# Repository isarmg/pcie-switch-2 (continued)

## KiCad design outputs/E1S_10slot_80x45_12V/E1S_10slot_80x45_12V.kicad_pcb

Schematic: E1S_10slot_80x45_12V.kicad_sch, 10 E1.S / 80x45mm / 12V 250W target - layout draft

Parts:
C1, C2: 10uF 25V X7R; C_1210_3225Metric
C101, C104, C107, C110, C113, C116, C119, C122, C125, C128, C301: 10nF 25V; C_0402_1005Metric
C102, C105, C108, C111, C114, C117, C120, C123, C126, C129: 100nF 50V; C_0603_1608Metric
C103, C106, C109, C112, C115, C118, C121, C124, C127, C130: 1uF 25V; C_0603_1608Metric
C311: 10uF 25V; C_0805_2012Metric
C312: 100nF 50V; C_0402_1005Metric
C313: 3.3nF 25V; C_0402_1005Metric
C314, C315: 47uF 16V; C_1210_3225Metric
D1, D2: SMBJ13CA; D_SMB
F1, F2: 20A 125V; Littelfuse_456_20A
J1, J2, J3, J4, J5, J6, J7, J8, J9, J10: HSEC6-028-01-S-DV-WT-TR; Samtec_HSEC6-028-01-S-DV-WT
J11: 12V 15A FEED A; WireSolder_2x_8x5_P12
J12: 12V 15A FEED B; WireSolder_2x_8x5_P12
L31: 2.2uH; L_Coilcraft_XAL4020-XXX
R101, R106, R111, R116, R121, R126, R131, R136, R141, R146, R301: 76.1k; R_0402_1005Metric
R102, R104, R107, R109, R112, R114, R117, R119, R122, R124, R127, R129, R132, R134, R137, R139, R142, R144, R147, R149, R302, R304: 10k; R_0402_1005Metric
R103, R108, R113, R118, R123, R128, R133, R138, R143, R148, R303: 102k; R_0402_1005Metric
R105, R110, R115, R120, R125, R130, R135, R140, R145, R150: 1.10k; R_0402_1005Metric
R305: 3.32k; R_0402_1005Metric
R311: 100k; R_0402_1005Metric
U1: FICTITIOUS_BGA256_RANDOM_PINOUT; FICTITIOUS_BGA256_37p5_P1_Sparse32_RANDOM
U11, U12, U13, U14, U15, U16, U17, U18, U19, U20, U30: TPS259470ARPWR; TI_RPW0010A_TPS25947
U31: TPS62132RGTR; VQFN-16-1EP_3x3mm_P0.5mm_EP1.68x1.68mm

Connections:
/AUX_12V_PROTECTED: C311.1, C312.1, U30.6 (OUT), U31.10, U31.11, U31.12, U31.13
/AUX_DVDT: C301.1, U30.7 (DVDT)
/AUX_ILM: R305.1, U30.9 (ILM)
/AUX_OV: R303.2, R304.1, U30.2 (OVLO)
/AUX_PG: R311.2, U31.4
/AUX_UV: R301.2, R302.1, U30.1 (EN_UVLO)
/BUCK_SS: C313.1, U31.9
/BUCK_SW: L31.1, U31.1, U31.2, U31.3
/GND: C1.2, C2.2, C101.2, C102.2, C103.2, C104.2, C105.2, C106.2, C107.2, C108.2, C109.2, C110.2, C111.2, C112.2, C113.2, C114.2, C115.2, C116.2, C117.2, C118.2, C119.2, C120.2, C121.2, C122.2, C123.2, C124.2, C125.2, C126.2, C127.2, C128.2, C129.2, C130.2, C301.2, C311.2, C312.2, C313.2, C314.2, C315.2, D1.2, D2.2, J1.A1, J1.A2, J1.A3, J1.A4, J1.A5, J1.A6, J1.A13, J1.A16, J1.A19, J1.A22, J1.A25, J1.A28, J1.B13, J1.B16, J1.B19, J1.B22, J1.B25, J1.B28, J2.A1, J2.A2, J2.A3, J2.A4, J2.A5, J2.A6, J2.A13, J2.A16, J2.A19, J2.A22, J2.A25, J2.A28, J2.B13, J2.B16, J2.B19, J2.B22, J2.B25, J2.B28, J3.A1, J3.A2, J3.A3, J3.A4, J3.A5, J3.A6, J3.A13, J3.A16, J3.A19, J3.A22, J3.A25, J3.A28, J3.B13, J3.B16, J3.B19, J3.B22, J3.B25, J3.B28, J4.A1, J4.A2, J4.A3, J4.A4, J4.A5, J4.A6, J4.A13, J4.A16, J4.A19, J4.A22, J4.A25, J4.A28, J4.B13, J4.B16, J4.B19, J4.B22, J4.B25, J4.B28, J5.A1, J5.A2, J5.A3, J5.A4, J5.A5, J5.A6, J5.A13, J5.A16, J5.A19, J5.A22, J5.A25, J5.A28, J5.B13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
/P3V3_AUX: C314.1, C315.1, J1.B11, J2.B11, J3.B11, J4.B11, J5.B11, J6.B11, J7.B11, J8.B11, J9.B11, J10.B11, L31.2, R311.1, U31.14
/P12_SLOT01: C103.1, J1.B1, J1.B2, J1.B3, J1.B4, J1.B5, J1.B6, U11.6 (OUT)
/P12_SLOT02: C106.1, J2.B1, J2.B2, J2.B3, J2.B4, J2.B5, J2.B6, U12.6 (OUT)
/P12_SLOT03: C109.1, J3.B1, J3.B2, J3.B3, J3.B4, J3.B5, J3.B6, U13.6 (OUT)
/P12_SLOT04: C112.1, J4.B1, J4.B2, J4.B3, J4.B4, J4.B5, J4.B6, U14.6 (OUT)
/P12_SLOT05: C115.1, J5.B1, J5.B2, J5.B3, J5.B4, J5.B5, J5.B6, U15.6 (OUT)
/P12_SLOT06: C118.1, J6.B1, J6.B2, J6.B3, J6.B4, J6.B5, J6.B6, U16.6 (OUT)
/P12_SLOT07: C121.1, J7.B1, J7.B2, J7.B3, J7.B4, J7.B5, J7.B6, U17.6 (OUT)
/P12_SLOT08: C124.1, J8.B1, J8.B2, J8.B3, J8.B4, J8.B5, J8.B6, U18.6 (OUT)
/P12_SLOT09: C127.1, J9.B1, J9.B2, J9.B3, J9.B4, J9.B5, J9.B6, U19.6 (OUT)
/P12_SLOT10: C130.1, J10.B1, J10.B2, J10.B3, J10.B4, J10.B5, J10.B6, U20.6 (OUT)
/S01_DUALPORTEN_N: J1.B9
/S01_LED: J1.A10
/S01_PERST0_N: J1.B10, U1.F23
/S01_PERST1_CLKREQ_N: J1.A11
/S01_PRSNT0_N: J1.A12
/S01_PWRDIS: J1.B12
/S01_PWR_DVDT: C101.1, U11.7 (DVDT)
/S01_PWR_ILM: R105.1, U11.9 (ILM)
/S01_PWR_OV: R103.2, R104.1, U11.2 (OVLO)
/S01_PWR_UV: R101.2, R102.1, U11.1 (EN_UVLO)
/S01_REFCLK0_N: J1.B14, U1.C19
/S01_REFCLK0_P: J1.B15, U1.C20
/S01_REFCLK1_N: J1.A14, U1.AF13
/S01_REFCLK1_P: J1.A15, U1.AF14
/S01_SMBCLK_I3CCLK: J1.A7
/S01_SMBDATA_I3CDATA: J1.A8
/S01_SMRST_N: J1.A9
/S01_SW_RX0_N: J1.A17, U1.C7
/S01_SW_RX0_P: J1.A18, U1.C8
/S01_SW_RX1_N: J1.A20, U1.AK1
/S01_SW_RX1_P: J1.A21, U1.AK2
/S01_SW_RX2_N: J1.A23, U1.AJ31
/S01_SW_RX2_P: J1.A24, U1.AJ32
/S01_SW_RX3_N: J1.A26, U1.B5
/S01_SW_RX3_P: J1.A27, U1.B6
/S01_SW_TX0_N: J1.B17, U1.AF5
/S01_SW_TX0_P: J1.B18, U1.AF6
/S01_SW_TX1_N: J1.B20, U1.B1
/S01_SW_TX1_P: J1.B21, U1.B2
/S01_SW_TX2_N: J1.B23, U1.AL23
/S01_SW_TX2_P: J1.B24, U1.AL24
/S01_SW_TX3_N: J1.B26, U1.AH9
/S01_SW_TX3_P: J1.B27, U1.AH10
/S02_DUALPORTEN_N: J2.B9
/S02_LED: J2.A10
/S02_PERST0_N: J2.B10, U1.F24
/S02_PERST1_CLKREQ_N: J2.A11
/S02_PRSNT0_N: J2.A12
/S02_PWRDIS: J2.B12
/S02_PWR_DVDT: C104.1, U12.7 (DVDT)
/S02_PWR_ILM: R110.1, U12.9 (ILM)
/S02_PWR_OV: R108.2, R109.1, U12.2 (OVLO)
/S02_PWR_UV: R106.2, R107.1, U12.1 (EN_UVLO)
/S02_REFCLK0_N: J2.B14, U1.AL13
/S02_REFCLK0_P: J2.B15, U1.AL14
/S02_REFCLK1_N: J2.A14, U1.AM21
/S02_REFCLK1_P: J2.A15, U1.AM22
/S02_SMBCLK_I3CCLK: J2.A7
/S02_SMBDATA_I3CDATA: J2.A8
/S02_SMRST_N: J2.A9
/S02_SW_RX0_N: J2.A17, U1.AM25
/S02_SW_RX0_P: J2.A18, U1.AM26
/S02_SW_RX1_N: J2.A20, U1.AL17
/S02_SW_RX1_P: J2.A21, U1.AL18
/S02_SW_RX2_N: J2.A23, U1.C5
/S02_SW_RX2_P: J2.A24, U1.C6
/S02_SW_RX3_N: J2.A26, U1.AK23
/S02_SW_RX3_P: J2.A27, U1.AK24
/S02_SW_TX0_N: J2.B17, U1.AL25
/S02_SW_TX0_P: J2.B18, U1.AL26
/S02_SW_TX1_N: J2.B20, U1.B31
/S02_SW_TX1_P: J2.B21, U1.B32
/S02_SW_TX2_N: J2.B23, U1.AM7
/S02_SW_TX2_P: J2.B24, U1.AM8
/S02_SW_TX3_N: J2.B26, U1.AH23
/S02_SW_TX3_P: J2.B27, U1.AH24
/S03_DUALPORTEN_N: J3.B9
/S03_LED: J3.A10
/S03_PERST0_N: J3.B10, U1.F17
/S03_PERST1_CLKREQ_N: J3.A11
/S03_PRSNT0_N: J3.A12
/S03_PWRDIS: J3.B12
/S03_PWR_DVDT: C107.1, U13.7 (DVDT)
/S03_PWR_ILM: R115.1, U13.9 (ILM)
/S03_PWR_OV: R113.2, R114.1, U13.2 (OVLO)
/S03_PWR_UV: R111.2, R112.1, U13.1 (EN_UVLO)
/S03_REFCLK0_N: J3.B14, U1.D23
/S03_REFCLK0_P: J3.B15, U1.D24
/S03_REFCLK1_N: J3.A14, U1.B9
/S03_REFCLK1_P: J3.A15, U1.B10
/S03_SMBCLK_I3CCLK: J3.A7
/S03_SMBDATA_I3CDATA: J3.A8
/S03_SMRST_N: J3.A9
/S03_SW_RX0_N: J3.A17, U1.AG15
/S03_SW_RX0_P: J3.A18, U1.AG16
/S03_SW_RX1_N: J3.A20, U1.C13
/S03_SW_RX1_P: J3.A21, U1.C14
/S03_SW_RX2_N: J3.A23, U1.C21
/S03_SW_RX2_P: J3.A24, U1.C22
/S03_SW_RX3_N: J3.A26, U1.A1
/S03_SW_RX3_P: J3.A27, U1.A2
/S03_SW_TX0_N: J3.B17, U1.AL11
/S03_SW_TX0_P: J3.B18, U1.AL12
/S03_SW_TX1_N: J3.B20, U1.D9
/S03_SW_TX1_P: J3.B21, U1.D10
/S03_SW_TX2_N: J3.B23, U1.AH1
/S03_SW_TX2_P: J3.B24, U1.AH2
/S03_SW_TX3_N: J3.B26, U1.D17
/S03_SW_TX3_P: J3.B27, U1.D18
/S04_DUALPORTEN_N: J4.B9
/S04_LED: J4.A10
/S04_PERST0_N: J4.B10, U1.F18
/S04_PERST1_CLKREQ_N: J4.A11
/S04_PRSNT0_N: J4.A12
/S04_PWRDIS: J4.B12
/S04_PWR_DVDT: C110.1, U14.7 (DVDT)
/S04_PWR_ILM: R120.1, U14.9 (ILM)
/S04_PWR_OV: R118.2, R119.1, U14.2 (OVLO)
/S04_PWR_UV: R116.2, R117.1, U14.1 (EN_UVLO)
/S04_REFCLK0_N: J4.B14, U1.AL3
/S04_REFCLK0_P: J4.B15, U1.AL4
/S04_REFCLK1_N: J4.A14, U1.AG17
/S04_REFCLK1_P: J4.A15, U1.AG18
/S04_SMBCLK_I3CCLK: J4.A7
/S04_SMBDATA_I3CDATA: J4.A8
/S04_SMRST_N: J4.A9
/S04_SW_RX0_N: J4.A17, U1.AH7
/S04_SW_RX0_P: J4.A18, U1.AH8
/S04_SW_RX1_N: J4.A20, U1.AF21
/S04_SW_RX1_P: J4.A21, U1.AF22
/S04_SW_RX2_N: J4.A23, U1.AM31
/S04_SW_RX2_P: J4.A24, U1.AM32
/S04_SW_RX3_N: J4.A26, U1.E31
/S04_SW_RX3_P: J4.A27, U1.E32
/S04_SW_TX0_N: J4.B17, U1.AF17
/S04_SW_TX0_P: J4.B18, U1.AF18
/S04_SW_TX1_N: J4.B20, U1.AM27
/S04_SW_TX1_P: J4.B21, U1.AM28
/S04_SW_TX2_N: J4.B23, U1.AF3
/S04_SW_TX2_P: J4.B24, U1.AF4
/S04_SW_TX3_N: J4.B26, U1.AK7
/S04_SW_TX3_P: J4.B27, U1.AK8
/S05_DUALPORTEN_N: J5.B9
/S05_LED: J5.A10
/S05_PERST0_N: J5.B10, U1.AH15
/S05_PERST1_CLKREQ_N: J5.A11
/S05_PRSNT0_N: J5.A12
/S05_PWRDIS: J5.B12
/S05_PWR_DVDT: C113.1, U15.7 (DVDT)
/S05_PWR_ILM: R125.1, U15.9 (ILM)
/S05_PWR_OV: R123.2, R124.1, U15.2 (OVLO)
/S05_PWR_UV: R121.2, R122.1, U15.1 (EN_UVLO)
/S05_REFCLK0_N: J5.B14, U1.A17
/S05_REFCLK0_P: J5.B15, U1.A18
/S05_REFCLK1_N: J5.A14, U1.AM29
/S05_REFCLK1_P: J5.A15, U1.AM30
/S05_SMBCLK_I3CCLK: J5.A7
/S05_SMBDATA_I3CDATA: J5.A8
/S05_SMRST_N: J5.A9
/S05_SW_RX0_N: J5.A17, U1.C23
/S05_SW_RX0_P: J5.A18, U1.C24
/S05_SW_RX1_N: J5.A20, U1.A25
/S05_SW_RX1_P: J5.A21, U1.A26
/S05_SW_RX2_N: J5.A23, U1.AL27
/S05_SW_RX2_P: J5.A24, U1.AL28
/S05_SW_RX3_N: J5.A26, U1.AJ15
/S05_SW_RX3_P: J5.A27, U1.AJ16
/S05_SW_TX0_N: J5.B17, U1.D7
/S05_SW_TX0_P: J5.B18, U1.D8
/S05_SW_TX1_N: J5.B20, U1.C1
/S05_SW_TX1_P: J5.B21, U1.C2
/S05_SW_TX2_N: J5.B23, U1.AM17
/S05_SW_TX2_P: J5.B24, U1.AM18
/S05_SW_TX3_N: J5.B26, U1.B21
/S05_SW_TX3_P: J5.B27, U1.B22
/S06_DUALPORTEN_N: J6.B9
/S06_LED: J6.A10
/S06_PERST0_N: J6.B10, U1.AH16
/S06_PERST1_CLKREQ_N: J6.A11
/S06_PRSNT0_N: J6.A12
/S06_PWRDIS: J6.B12
/S06_PWR_DVDT: C116.1, U16.7 (DVDT)
/S06_PWR_ILM: R130.1, U16.9 (ILM)
/S06_PWR_OV: R128.2, R129.1, U16.2 (OVLO)
/S06_PWR_UV: R126.2, R127.1, U16.1 (EN_UVLO)
/S06_REFCLK0_N: J6.B14, U1.AK29
/S06_REFCLK0_P: J6.B15, U1.AK30
/S06_REFCLK1_N: J6.A14, U1.AF29
/S06_REFCLK1_P: J6.A15, U1.AF30
/S06_SMBCLK_I3CCLK: J6.A7
/S06_SMBDATA_I3CDATA: J6.A8
/S06_SMRST_N: J6.A9
/S06_SW_RX0_N: J6.A17, U1.A27
/S06_SW_RX0_P: J6.A18, U1.A28
/S06_SW_RX1_N: J6.A20, U1.AG9
/S06_SW_RX1_P: J6.A21, U1.AG10
/S06_SW_RX2_N: J6.A23, U1.C25
/S06_SW_RX2_P: J6.A24, U1.C26
/S06_SW_RX3_N: J6.A26, U1.AF11
/S06_SW_RX3_P: J6.A27, U1.AF12
/S06_SW_TX0_N: J6.B17, U1.B19
/S06_SW_TX0_P: J6.B18, U1.B20
/S06_SW_TX1_N: J6.B20, U1.A29
/S06_SW_TX1_P: J6.B21, U1.A30
/S06_SW_TX2_N: J6.B23, U1.A15
/S06_SW_TX2_P: J6.B24, U1.A16
/S06_SW_TX3_N: J6.B26, U1.C31
/S06_SW_TX3_P: J6.B27, U1.C32
/S07_DUALPORTEN_N: J7.B9
/S07_LED: J7.A10
/S07_PERST0_N: J7.B10, U1.E25
/S07_PERST1_CLKREQ_N: J7.A11
/S07_PRSNT0_N: J7.A12
/S07_PWRDIS: J7.B12
/S07_PWR_DVDT: C119.1, U17.7 (DVDT)
/S07_PWR_ILM: R135.1, U17.9 (ILM)
/S07_PWR_OV: R133.2, R134.1, U17.2 (OVLO)
/S07_PWR_UV: R131.2, R132.1, U17.1 (EN_UVLO)
/S07_REFCLK0_N: J7.B14, U1.B17
/S07_REFCLK0_P: J7.B15, U1.B18
/S07_REFCLK1_N: J7.A14, U1.AG31
/S07_REFCLK1_P: J7.A15, U1.AG32
/S07_SMBCLK_I3CCLK: J7.A7
/S07_SMBDATA_I3CDATA: J7.A8
/S07_SMRST_N: J7.A9
/S07_SW_RX0_N: J7.A17, U1.E23
/S07_SW_RX0_P: J7.A18, U1.E24
/S07_SW_RX1_N: J7.A20, U1.AK21
/S07_SW_RX1_P: J7.A21, U1.AK22
/S07_SW_RX2_N: J7.A23, U1.AL31
/S07_SW_RX2_P: J7.A24, U1.AL32
/S07_SW_RX3_N: J7.A26, U1.AJ17
/S07_SW_RX3_P: J7.A27, U1.AJ18
/S07_SW_TX0_N: J7.B17, U1.AK15
/S07_SW_TX0_P: J7.B18, U1.AK16
/S07_SW_TX1_N: J7.B20, U1.AH25
/S07_SW_TX1_P: J7.B21, U1.AH26
/S07_SW_TX2_N: J7.B23, U1.AG1
/S07_SW_TX2_P: J7.B24, U1.AG2
/S07_SW_TX3_N: J7.B26, U1.AF19
/S07_SW_TX3_P: J7.B27, U1.AF20
/S08_DUALPORTEN_N: J8.B9
/S08_LED: J8.A10
/S08_PERST0_N: J8.B10, U1.E26
/S08_PERST1_CLKREQ_N: J8.A11
/S08_PRSNT0_N: J8.A12
/S08_PWRDIS: J8.B12
/S08_PWR_DVDT: C122.1, U18.7 (DVDT)
/S08_PWR_ILM: R140.1, U18.9 (ILM)
/S08_PWR_OV: R138.2, R139.1, U18.2 (OVLO)
/S08_PWR_UV: R136.2, R137.1, U18.1 (EN_UVLO)
/S08_REFCLK0_N: J8.B14, U1.B27
/S08_REFCLK0_P: J8.B15, U1.B28
/S08_REFCLK1_N: J8.A14, U1.AM15
/S08_REFCLK1_P: J8.A15, U1.AM16
/S08_SMBCLK_I3CCLK: J8.A7
/S08_SMBDATA_I3CDATA: J8.A8
/S08_SMRST_N: J8.A9
/S08_SW_RX0_N: J8.A17, U1.B13
/S08_SW_RX0_P: J8.A18, U1.B14
/S08_SW_RX1_N: J8.A20, U1.F31
/S08_SW_RX1_P: J8.A21, U1.F32
/S08_SW_RX2_N: J8.A23, U1.AF15
/S08_SW_RX2_P: J8.A24, U1.AF16
/S08_SW_RX3_N: J8.A26, U1.C17
/S08_SW_RX3_P: J8.A27, U1.C18
/S08_SW_TX0_N: J8.B17, U1.AL19
/S08_SW_TX0_P: J8.B18, U1.AL20
/S08_SW_TX1_N: J8.B20, U1.AH31
/S08_SW_TX1_P: J8.B21, U1.AH32
/S08_SW_TX2_N: J8.B23, U1.AL21
/S08_SW_TX2_P: J8.B24, U1.AL22
/S08_SW_TX3_N: J8.B26, U1.AL29
/S08_SW_TX3_P: J8.B27, U1.AL30
/S09_DUALPORTEN_N: J9.B9
/S09_LED: J9.A10
/S09_PERST0_N: J9.B10, U1.AK3
/S09_PERST1_CLKREQ_N: J9.A11
/S09_PRSNT0_N: J9.A12
/S09_PWRDIS: J9.B12
/S09_PWR_DVDT: C125.1, U19.7 (DVDT)
/S09_PWR_ILM: R145.1, U19.9 (ILM)
/S09_PWR_OV: R143.2, R144.1, U19.2 (OVLO)
/S09_PWR_UV: R141.2, R142.1, U19.1 (EN_UVLO)
/S09_REFCLK0_N: J9.B14, U1.C27
/S09_REFCLK0_P: J9.B15, U1.C28
/S09_REFCLK1_N: J9.A14, U1.AG7
/S09_REFCLK1_P: J9.A15, U1.AG8
/S09_SMBCLK_I3CCLK: J9.A7
/S09_SMBDATA_I3CDATA: J9.A8
/S09_SMRST_N: J9.A9
/S09_SW_RX0_N: J9.A17, U1.AK27
/S09_SW_RX0_P: J9.A18, U1.AK28
/S09_SW_RX1_N: J9.A20, U1.C11
/S09_SW_RX1_P: J9.A21, U1.C12
/S09_SW_RX2_N: J9.A23, U1.A21
/S09_SW_RX2_P: J9.A24, U1.A22
/S09_SW_RX3_N: J9.A26, U1.F1
/S09_SW_RX3_P: J9.A27, U1.F2
/S09_SW_TX0_N: J9.B17, U1.AK13
/S09_SW_TX0_P: J9.B18, U1.AK14
/S09_SW_TX1_N: J9.B20, U1.E1
/S09_SW_TX1_P: J9.B21, U1.E2
/S09_SW_TX2_N: J9.B23, U1.B23
/S09_SW_TX2_P: J9.B24, U1.B24
/S09_SW_TX3_N: J9.B26, U1.C15
/S09_SW_TX3_P: J9.B27, U1.C16
/S10_DUALPORTEN_N: J10.B9
/S10_LED: J10.A10
/S10_PERST0_N: J10.B10, U1.AK4
/S10_PERST1_CLKREQ_N: J10.A11
/S10_PRSNT0_N: J10.A12
/S10_PWRDIS: J10.B12
/S10_PWR_DVDT: C128.1, U20.7 (DVDT)
/S10_PWR_ILM: R150.1, U20.9 (ILM)
/S10_PWR_OV: R148.2, R149.1, U20.2 (OVLO)
/S10_PWR_UV: R146.2, R147.1, U20.1 (EN_UVLO)
/S10_REFCLK0_N: J10.B14, U1.A9
/S10_REFCLK0_P: J10.B15, U1.A10
/S10_REFCLK1_N: J10.A14, U1.A13
/S10_REFCLK1_P: J10.A15, U1.A14
/S10_SMBCLK_I3CCLK: J10.A7
/S10_SMBDATA_I3CDATA: J10.A8
/S10_SMRST_N: J10.A9
/S10_SW_RX0_N: J10.A17, U1.AG25
/S10_SW_RX0_P: J10.A18, U1.AG26
/S10_SW_RX1_N: J10.A20, U1.A11
/S10_SW_RX1_P: J10.A21, U1.A12
/S10_SW_RX2_N: J10.A23, U1.AM11
/S10_SW_RX2_P: J10.A24, U1.AM12
/S10_SW_RX3_N: J10.A26, U1.AF1
/S10_SW_RX3_P: J10.A27, U1.AF2
/S10_SW_TX0_N: J10.B17, U1.A31
/S10_SW_TX0_P: J10.B18, U1.A32
/S10_SW_TX1_N: J10.B20, U1.F9
/S10_SW_TX1_P: J10.B21, U1.F10
/S10_SW_TX2_N: J10.B23, U1.AF9
/S10_SW_TX2_P: J10.B24, U1.AF10
/S10_SW_TX3_N: J10.B26, U1.AL15
/S10_SW_TX3_P: J10.B27, U1.AL16
/VBANK_A: C1.1, C102.1, C105.1, C108.1, C111.1, C114.1, D1.1, F1.2, R101.1, R103.1, R106.1, R108.1, R111.1, R113.1, R116.1, R118.1, R121.1, R123.1, R301.1, R303.1, U11.5 (IN), U12.5 (IN), U13.5 (IN), U14.5 (IN), U15.5 (IN), U30.5 (IN)
/VBANK_B: C2.1, C117.1, C120.1, C123.1, C126.1, C129.1, D2.1, F2.2, R126.1, R128.1, R131.1, R133.1, R136.1, R138.1, R141.1, R143.1, R146.1, R148.1, U16.5 (IN), U17.5 (IN), U18.5 (IN), U19.5 (IN), U20.5 (IN)
/VIN_A: F1.1, J11.1
/VIN_B: F2.1, J12.1

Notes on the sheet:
SLOT 01 / J1 / PCIe x4 + 25W POWER / B7,B8 NC
SLOT 02 / J2 / PCIe x4 + 25W POWER / B7,B8 NC
SLOT 03 / J3 / PCIe x4 + 25W POWER / B7,B8 NC
SLOT 04 / J4 / PCIe x4 + 25W POWER / B7,B8 NC
SLOT 05 / J5 / PCIe x4 + 25W POWER / B7,B8 NC
SLOT 06 / J6 / PCIe x4 + 25W POWER / B7,B8 NC
SLOT 07 / J7 / PCIe x4 + 25W POWER / B7,B8 NC
SLOT 08 / J8 / PCIe x4 + 25W POWER / B7,B8 NC
SLOT 09 / J9 / PCIe x4 + 25W POWER / B7,B8 NC
SLOT 10 / J10 / PCIe x4 + 25W POWER / B7,B8 NC
U1 FICTITIOUS BGA256 / USER-REQUESTED RANDOM BALL MAP / NOT A REAL SWITCH
12V INPUT / 10 x 25W / SLOT POWER DESIGN - FICTITIOUS SWITCH HAS NO SUPPLY PINOUT

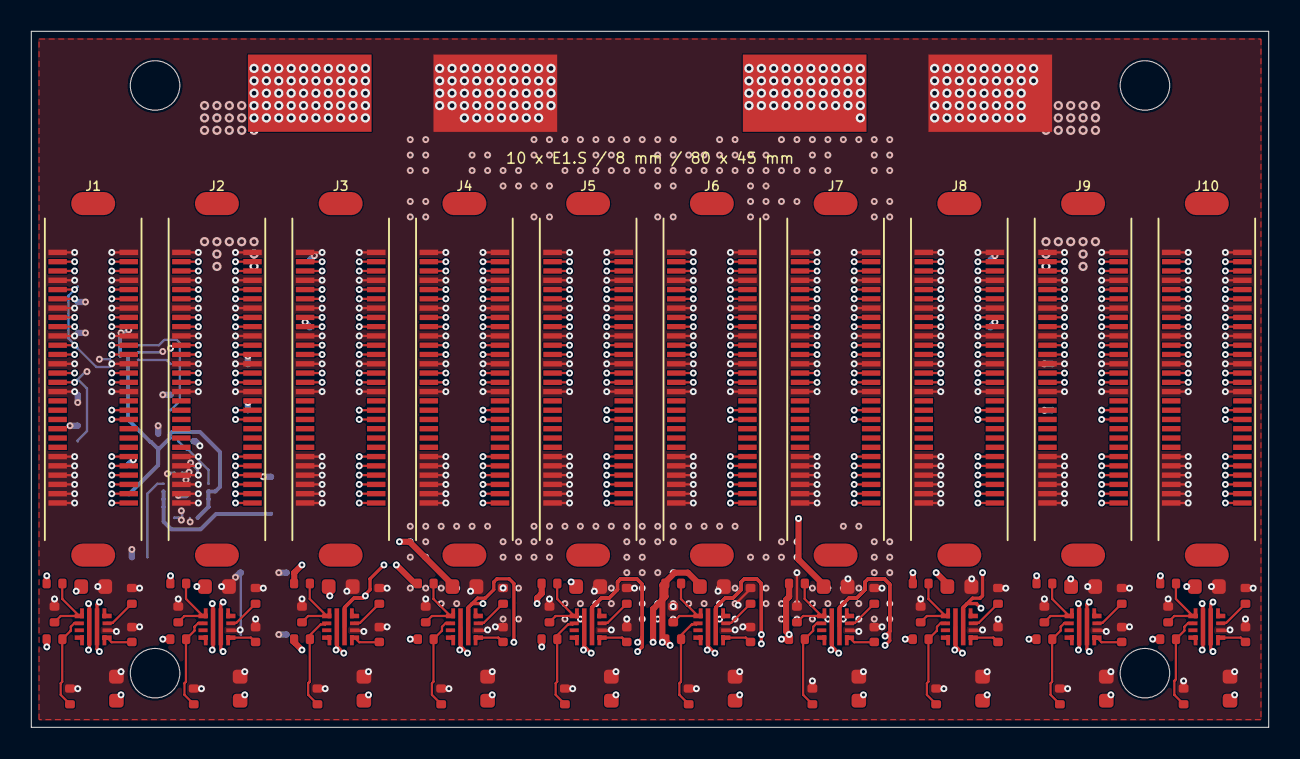
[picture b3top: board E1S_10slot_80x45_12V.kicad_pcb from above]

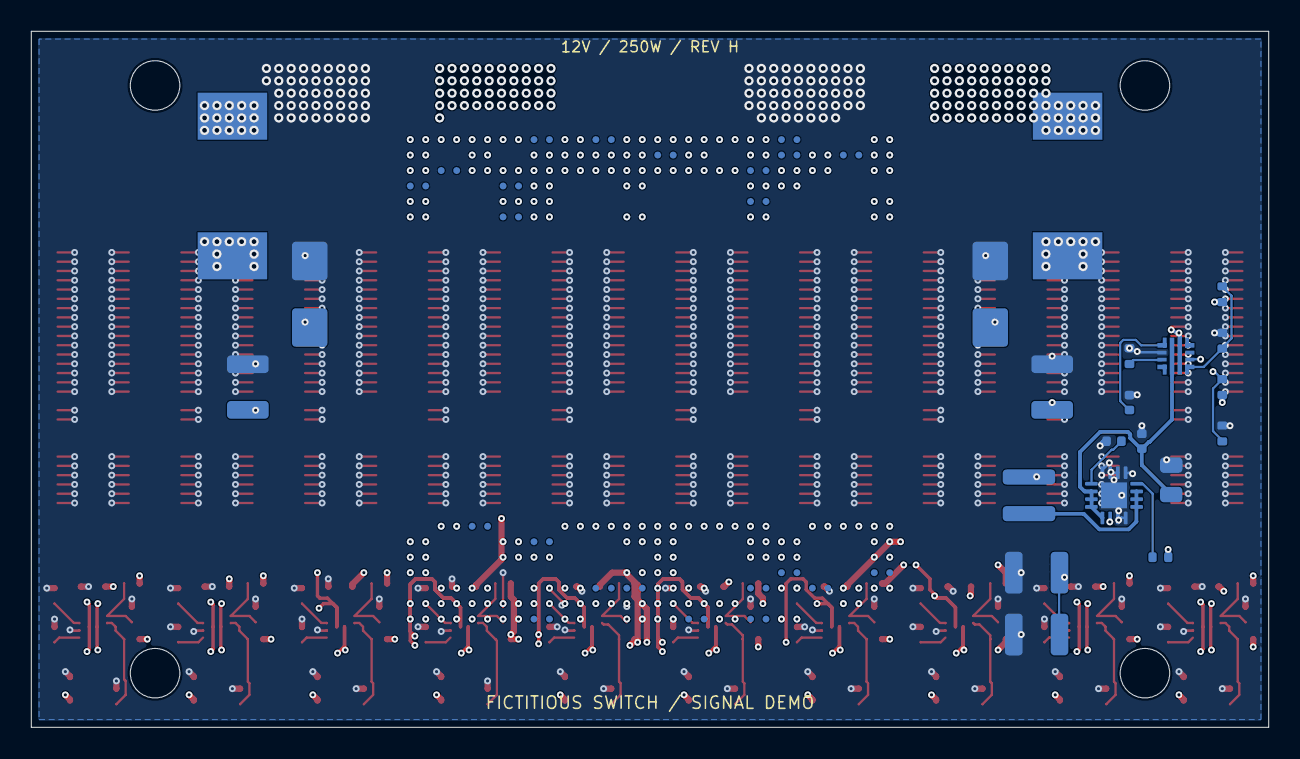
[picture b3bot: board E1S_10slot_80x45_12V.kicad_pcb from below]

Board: 20 copper layers, 80.0 x 45.0 mm, 128 parts (22 on the bottom side), 274 nets.

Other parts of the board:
H1, H2, H3, H4: M3 NPTH

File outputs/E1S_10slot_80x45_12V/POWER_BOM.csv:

Reference,Value,MPN_or_specification,Footprint,Side,Height_envelope_mm,X_mm,Y_mm,Datasheet
J11,12V 15A FEED A,12V 15A FEED A,WireSolder_2x_8x5_P12,F,0,24,4,
F1,20A 125V,0456020.ER,Littelfuse_456_20A,B,3.5,13,10,https://www.littelfuse.com/assetdocs/littelfuse_fuse_456_dat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
D1,SMBJ13CA,SMBJ13CA,D_SMB,B,2.5,18,17,https://www.littelfuse.com/products/tvs-diodes/surface-mount/smbj
C1,10uF 25V X7R,GRM32ER71E106KA12,C_1210_3225Metric,B,2.8,14,23,
J12,12V 15A FEED B,12V 15A FEED B,WireSolder_2x_8x5_P12,F,0,56,4,
F2,20A 125V,0456020.ER,Littelfuse_456_20A,B,3.5,67,10,https://www.littelfuse.com/assetdocs/littelfuse_fuse_456_dat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
D2,SMBJ13CA,SMBJ13CA,D_SMB,B,2.5,62,17,https://www.littelfuse.com/products/tvs-diodes/surface-mount/smbj
C2,10uF 25V X7R,GRM32ER71E106KA12,C_1210_3225Metric,B,2.8,66,23,
U11,TPS259470ARPWR,TPS259470ARPWR,TI_RPW0010A_TPS25947,F,1,4,38.5,https://www.ti.com/lit/ds/symlink/tps25947.pdf
R101,76.1k,76.1k,R_0402_1005Metric,F,0.4,1.5,35.7,
R102,10k,10k,R_0402_1005Metric,F,0.4,1.5,37.7,
R103,102k,102k,R_0402_1005Metric,F,0.4,1.5,39.3,
R104,10k,10k,R_0402_1005Metric,F,0.4,2.5,43,
R105,1.10k,1.10k,R_0402_1005Metric,F,0.4,6.5,36.5,
C101,10nF 25V,10nF 25V,C_0402_1005Metric,F,0.55,6.5,39,
C102,100nF 50V,100nF 50V,C_0603_1608Metric,F,0.9,4,35.9,
C103,1uF 25V,1uF 25V,C_0603_1608Metric,F,0.9,5.5,42.5,
U12,TPS259470ARPWR,TPS259470ARPWR,TI_RPW0010A_TPS25947,F,1,12,38.5,https://www.ti.com/lit/ds/symlink/tps25947.pdf
R106,76.1k,76.1k,R_0402_1005Metric,F,0.4,9.5,35.7,
R107,10k,10k,R_0402_1005Metric,F,0.4,9.5,37.7,
R108,102k,102k,R_0402_1005Metric,F,0.4,9.5,39.3,
R109,10k,10k,R_0402_1005Metric,F,0.4,10.5,43,
R110,1.10k,1.10k,R_0402_1005Metric,F,0.4,14.5,36.5,
C104,10nF 25V,10nF 25V,C_0402_1005Metric,F,0.55,14.5,39,
C105,100nF 50V,100nF 50V,C_0603_1608Metric,F,0.9,12,35.9,
C106,1uF 25V,1uF 25V,C_0603_1608Metric,F,0.9,13.5,42.5,
U13,TPS259470ARPWR,TPS259470ARPWR,TI_RPW0010A_TPS25947,F,1,20,38.5,https://www.ti.com/lit/ds/symlink/tps25947.pdf
R111,76.1k,76.1k,R_0402_1005Metric,F,0.4,17.5,35.7,
R112,10k,10k,R_0402_1005Metric,F,0.4,17.5,37.7,
R113,102k,102k,R_0402_1005Metric,F,0.4,17.5,39.3,
R114,10k,10k,R_0402_1005Metric,F,0.4,18.5,43,
R115,1.10k,1.10k,R_0402_1005Metric,F,0.4,22.5,36.5,
C107,10nF 25V,10nF 25V,C_0402_1005Metric,F,0.55,22.5,39,
C108,100nF 50V,100nF 50V,C_0603_1608Metric,F,0.9,20,35.9,
C109,1uF 25V,1uF 25V,C_0603_1608Metric,F,0.9,21.5,42.5,
U14,TPS259470ARPWR,TPS259470ARPWR,TI_RPW0010A_TPS25947,F,1,28,38.5,https://www.ti.com/lit/ds/symlink/tps25947.pdf
R116,76.1k,76.1k,R_0402_1005Metric,F,0.4,25.5,35.7,
R117,10k,10k,R_0402_1005Metric,F,0.4,25.5,37.7,
R118,102k,102k,R_0402_1005Metric,F,0.4,25.5,39.3,
R119,10k,10k,R_0402_1005Metric,F,0.4,26.5,43,
R120,1.10k,1.10k,R_0402_1005Metric,F,0.4,30.5,36.5,
C110,10nF 25V,10nF 25V,C_0402_1005Metric,F,0.55,30.5,39,
C111,100nF 50V,100nF 50V,C_0603_1608Metric,F,0.9,28,35.9,
C112,1uF 25V,1uF 25V,C_0603_1608Metric,F,0.9,29.5,42.5,
U15,TPS259470ARPWR,TPS259470ARPWR,TI_RPW0010A_TPS25947,F,1,36,38.5,https://www.ti.com/lit/ds/symlink/tps25947.pdf
R121,76.1k,76.1k,R_0402_1005Metric,F,0.4,33.5,35.7,
R122,10k,10k,R_0402_1005Metric,F,0.4,33.5,37.7,
R123,102k,102k,R_0402_1005Metric,F,0.4,33.5,39.3,
R124,10k,10k,R_0402_1005Metric,F,0.4,34.5,43,
R125,1.10k,1.10k,R_0402_1005Metric,F,0.4,38.5,36.5,
C113,10nF 25V,10nF 25V,C_0402_1005Metric,F,0.55,38.5,39,
C114,100nF 50V,100nF 50V,C_0603_1608Metric,F,0.9,36,35.9,
C115,1uF 25V,1uF 25V,C_0603_1608Metric,F,0.9,37.5,42.5,
U16,TPS259470ARPWR,TPS259470ARPWR,TI_RPW0010A_TPS25947,F,1,44,38.5,https://www.ti.com/lit/ds/symlink/tps25947.pdf
R126,76.1k,76.1k,R_0402_1005Metric,F,0.4,41.5,35.7,
R127,10k,10k,R_0402_1005Metric,F,0.4,41.5,37.7,
R128,102k,102k,R_0402_1005Metric,F,0.4,41.5,39.3,
R129,10k,10k,R_0402_1005Metric,F,0.4,42.5,43,
R130,1.10k,1.10k,R_0402_1005Metric,F,0.4,46.5,36.5,
C116,10nF 25V,10nF 25V,C_0402_1005Metric,F,0.55,46.5,39,
C117,100nF 50V,100nF 50V,C_0603_1608Metric,F,0.9,44,35.9,
C118,1uF 25V,1uF 25V,C_0603_1608Metric,F,0.9,45.5,42.5,
U17,TPS259470ARPWR,TPS259470ARPWR,TI_RPW0010A_TPS25947,F,1,52,38.5,https://www.ti.com/lit/ds/symlink/tps25947.pdf
R131,76.1k,76.1k,R_0402_1005Metric,F,0.4,49.5,35.7,
R132,10k,10k,R_0402_1005Metric,F,0.4,49.5,37.7,
R133,102k,102k,R_0402_1005Metric,F,0.4,49.5,39.3,
R134,10k,10k,R_0402_1005Metric,F,0.4,50.5,43,
R135,1.10k,1.10k,R_0402_1005Metric,F,0.4,54.5,36.5,
C119,10nF 25V,10nF 25V,C_0402_1005Metric,F,0.55,54.5,39,
C120,100nF 50V,100nF 50V,C_0603_1608Metric,F,0.9,52,35.9,
C121,1uF 25V,1uF 25V,C_0603_1608Metric,F,0.9,53.5,42.5,
U18,TPS259470ARPWR,TPS259470ARPWR,TI_RPW0010A_TPS25947,F,1,60,38.5,https://www.ti.com/lit/ds/symlink/tps25947.pdf
R136,76.1k,76.1k,R_0402_1005Metric,F,0.4,57.5,35.7,
R137,10k,10k,R_0402_1005Metric,F,0.4,57.5,37.7,
R138,102k,102k,R_0402_1005Metric,F,0.4,57.5,39.3,
R139,10k,10k,R_0402_1005Metric,F,0.4,58.5,43,
R140,1.10k,1.10k,R_0402_1005Metric,F,0.4,62.5,36.5,
C122,10nF 25V,10nF 25V,C_0402_1005Metric,F,0.55,62.5,39,
C123,100nF 50V,100nF 50V,C_0603_1608Metric,F,0.9,60,35.9,
C124,1uF 25V,1uF 25V,C_0603_1608Metric,F,0.9,61.5,42.5,
U19,TPS259470ARPWR,TPS259470ARPWR,TI_RPW0010A_TPS25947,F,1,68,38.5,https://www.ti.com/lit/ds/symlink/tps25947.pdf
R141,76.1k,76.1k,R_0402_1005Metric,F,0.4,65.5,35.7,
R142,10k,10k,R_0402_1005Metric,F,0.4,65.5,37.7,
R143,102k,102k,R_0402_1005Metric,F,0.4,65.5,39.3,
R144,10k,10k,R_0402_1005Metric,F,0.4,66.5,43,
R145,1.10k,1.10k,R_0402_1005Metric,F,0.4,70.5,36.5,
C125,10nF 25V,10nF 25V,C_0402_1005Metric,F,0.55,70.5,39,
C126,100nF 50V,100nF 50V,C_0603_1608Metric,F,0.9,68,35.9,
C127,1uF 25V,1uF 25V,C_0603_1608Metric,F,0.9,69.5,42.5,
U20,TPS259470ARPWR,TPS259470ARPWR,TI_RPW0010A_TPS25947,F,1,76,38.5,https://www.ti.com/lit/ds/symlink/tps25947.pdf
R146,76.1k,76.1k,R_0402_1005Metric,F,0.4,73.5,35.7,
R147,10k,10k,R_0402_1005Metric,F,0.4,73.5,37.7,
R148,102k,102k,R_0402_1005Metric,F,0.4,73.5,39.3,
R149,10k,10k,R_0402_1005Metric,F,0.4,74.5,43,
R150,1.10k,1.10k,R_0402_1005Metric,F,0.4,78.5,36.5,
C128,10nF 25V,10nF 25V,C_0402_1005Metric,F,0.55,78.5,39,
C129,100nF 50V,100nF 50V,C_0603_1608Metric,F,0.9,76,35.9,
C130,1uF 25V,1uF 25V,C_0603_1608Metric,F,0.9,77.5,42.5,
U30,TPS259470ARPWR,TPS259470ARPWR,TI_RPW0010A_TPS25947,B,1,6,21,https://www.ti.com/lit/ds/symlink/tps25947.pdf
R301,76.1k,76.1k,R_0402_1005Metric,B,0.4,3,17,
R302,10k,10k,R_0402_1005Metric,B,0.4,3,20,
R303,102k,102k,R_0402_1005Metric,B,0.4,3,23,
R304,10k,10k,R_0402_1005Metric,B,0.4,3,26,
R305,3.32k,3.32k,R_0402_1005Metric,B,0.4,9,21,
C301,10nF 25V,10nF 25V,C_0402_1005Metric,B,0.55,9,24,
U31,TPS62132RGTR,TPS62132RGTR,VQFN-16-1EP_3x3mm_P0.5mm_EP1.68x1.68mm,B,1,10,30,https://www.ti.com/lit/ds/symlink/tps62130.pdf
L31,2.2uH,XAL4020-222MEC,L_Coilcraft_XAL4020-XXX,B,2.1,15.5,30,https://www.coilcraft.com/getmedia/6adcb47d-8b55-416c-976e-1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
C311,10uF 25V,10uF 25V,C_0805_2012Metric,B,1.45,6.3,29,
C312,100nF 50V,100nF 50V,C_0402_1005Metric,B,0.55,8.2,26.5,
C313,3.3nF 25V,3.3nF 25V,C_0402_1005Metric,B,0.55,10,26.5,
C314,47uF 16V,47uF 16V,C_1210_3225Metric,B,2.8,15,35,
C315,47uF 16V,47uF 16V,C_1210_3225Metric,B,2.8,15,39,
R311,100k,100k,R_0402_1005Metric,B,0.4,7,34,

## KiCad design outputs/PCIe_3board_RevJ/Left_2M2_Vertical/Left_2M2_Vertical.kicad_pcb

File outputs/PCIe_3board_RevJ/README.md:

# Rev J：19.5 × 45 mm 直立 M.2 小板

本版优先满足尺寸要求，将六个 M-Key 插槽换成 Amphenol MDT350M01001VT 的 Gen4 候选方案。两块小板均为 **19.5 × 45 mm**，三个连接器全部在正面、朝上，中心距 **6.2 mm**，硬盘平面与 E1.S 插槽平行。主板保持 **80 × 45 mm、10 个 E1.S 槽、8 mm 中心距**，没有 E1.S 硬盘模型或四角安装孔。

这是 KiCad 10 的结构、供电及连接布局草案，使用用户允许的虚构 BGA。不是可工作的 PCIe switch 产品，不能直接投板。检查结果见 `VALIDATION.json`、各板 `DRC.json` 和 `STEP_VALIDATION.json`，不要沿用 Rev I 的检查结论。

| 工程目录（保留旧名以兼容路径） | 外形 | 铜层 | 接口 |
|---|---|---|---|
| Main_10E1S | 80 × 45 mm | 32 | 10 × E1.S x4，虚构 BGA400，共 64 lane |
| Left_2M2_Vertical | 19.5 × 45 mm | 32 | J1/M1、J2/M2、J4/M4，三个下行 M-Key x4 |
| Right_M2_Upstream | 19.5 × 45 mm | 32 | J3/M3、J5/M5 为下行，J4/UP 为上行，均直立 |
| Assembly_View | 三块独立板的装配展示 | 仅展示 | 五个 SSD 包络，上行槽留空，54 对 twinax 包络 |

## 尺寸与连接器

三个连接器中心为 (3.55,17)、(9.75,17)、(15.95,17) mm，板面内旋转 90°。19.5 mm 为 PCB 外形宽度，不包含线束、机壳和插入后的 SSD。M.2 板体包络为 22 × 80 × 0.8 mm，上端约高于子板顶面 82.84 mm；需机壳上部支撑。

依据 [Amphenol 产品页](https://www.amphenol-cs.com/product/mdt350m01001vt.html)及[厂家客户图 CMDT350X0X001VT Rev 2（Farnell 托管副本）](https://www.farnell.com/cad/2913906.pdf)，本体为 **24.2 × 3.5 × 5.5 mm**，0.5 mm 同排间距，焊盘 0.30 × 1.375 mm，带 1.60/1.10 mm 定位孔和两端固定焊盘。产品页标称 16 Gb/s，因此本版按 Gen4 候选选用，未验证完整通道。图纸副本在 `references/Amphenol_MDT350_Farnell.pdf`。

焊盘几何依据厂家图重建；该图没有逐脚编号，编号方向按 M.2 卡端约定推定，必须由厂商编号图或实物再次确认。STEP 为尺寸包络，不是厂家精细 CAD。局部 DRC 规则仅对同一个 MDT350 封装内部孔到焊盘使用 0.05 mm（厂家图的实际最小间距），另对盲埋孔间的孔到铜设 0.20 mm HDI 目标，孔到孔仍为 0.25 mm；普通孔到铜仍为 0.25 mm；需板厂确认钻孔及公差。

主板按此前要求取消了 E1.S 固定/定位孔，现用 E1.S 器件仍须修改安装方式。小板六个孔是 M.2 连接器必需的定位孔，不是四角安装孔。

## PCIe 与线束

每侧 **12 lane = 三组独立 x4**，不是协议层的单条 x12 链路。每侧有 **24 对数据 twinax + 3 对 REFCLK twinax**，共 27 对差分线，另配 12 芯控制/地线和独立 12 V/GND 电源线。

`TWINAX_MAP.csv` 列出 54 对线的两端焊盘、P/N 和方向。主板 J301→左板 J50、J302→右板 J50，1 为受保护 12 V，2 为地。控制 J303→左板 J51、J304→右板 J51：1–3、4–6、7–9 为三个端口的 PERST/CLKREQ/WAKE，10–12 为地。左侧端口顺序 M1/M2/M4，右侧为 M3/UP/M5，右侧控制顺序与物理排列不同，按针号接线。

总计 64 lane：40 给 E1.S、20 给五个 M.2 SSD、4 用于上行。十五个下行 SSD 共享单条 x4 上行带宽。BGA400 不对应 PEX88064、PEX90048 或其他真实芯片。新增信号使用其空闲虚构球位。

TX/RX 从 switch 视角命名。右板 J4 上行槽的 PET 接 switch RX、PER 接经交流耦合的 switch TX，REFCLK/PERST 来自主机。J4 的 3.3 V 触点不连接，避免反灌电。上行槽需要带 M.2 金手指的直通线/转接模块，不能插 SSD 当作下行使用。

## 供电、高度与限制

主板保留 12 V 输入、双路 20 A 保险、每个 E1.S 槽的 eFuse、3.3 V AUX，十槽各 25 W、合计 250 W 的设计目标。子板供电在主板上由 TPS259470A eFuse 保护，左侧约 5 A、右侧约 3.5 A 名义限流。

五个 M.2 各用 TPS565201 的 12 V→3.3 V 降压电路，含 2.2 µH XAL5030-222MEC、输入去耦、自举电容、两个 22 µF 输出电容和反馈电阻。每槽暂按 4 A/13.2 W 预留，未验证持续输出。五槽共 66 W 输出；若效率按 90% 估算，总 SSD 输入预算约 **323 W**，尚未计真实 switch、风扇和余量。

背面元件包络约 3.1–3.5 mm，低于 8 mm；M.2 连接器高 5.5 mm。E1.S 连接器约 9.05 mm，按此前约定不计入限制。SSD 及线束高度另计。

小板使用焊盘内盲孔、埋孔和独立 3.3 V 电源层。层数、1.6 mm 厚度是 CAD 参数，未获得板厂叠层及工艺确认。当前走线只表达连接关系，没有完成差分等长、85 Ω 阻抗设计、过孔残桩、PCIe Gen4 损耗/串扰验证。供电布局仍须按芯片厂家建议进一步收紧，并验证电容有效容量、载流、启动、温升和散热。虚构 BGA 没有真实 switch 的核心供电、时钟或固件实现。

## 打开文件

打开三个电气工程目录中同名 `.kicad_pro`。各板同名 `.step` 是单板模型；`Assembly_View/Assembly_View.step` 是装配展示，装配 PCB 不用于制造。线束仅表示连接方向和大致路径，没有确定出口、弯曲半径、接头或应力释放结构。

连接原理图采用被动引脚类型，ERC 不验证 PCIe 逻辑、电源时序或实际器件兼容性。不得将 DRC/网表通过解释为 PCIe Gen4 或满载供电已验证。

本版三块板的本机 KiCad DRC 均为 0 违规、0 未连接；2104 个已连接引脚与原理图网表一致，54 对线束映射两端一致。ERC 均无错误，主板保留 80 个管理信号相关警告，两块小板无 ERC 警告。具体记录见 `VALIDATION.json`。

工程位于 `C:\Users\micro\Desktop\方案\pcie switch 2`，此前迁移与 `.gitignore` 更新保留。Rev I 未覆盖，Rev J 独立交付。

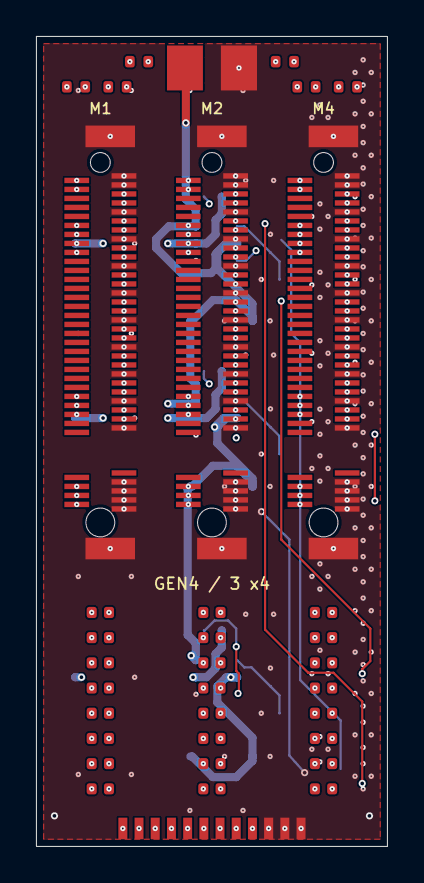
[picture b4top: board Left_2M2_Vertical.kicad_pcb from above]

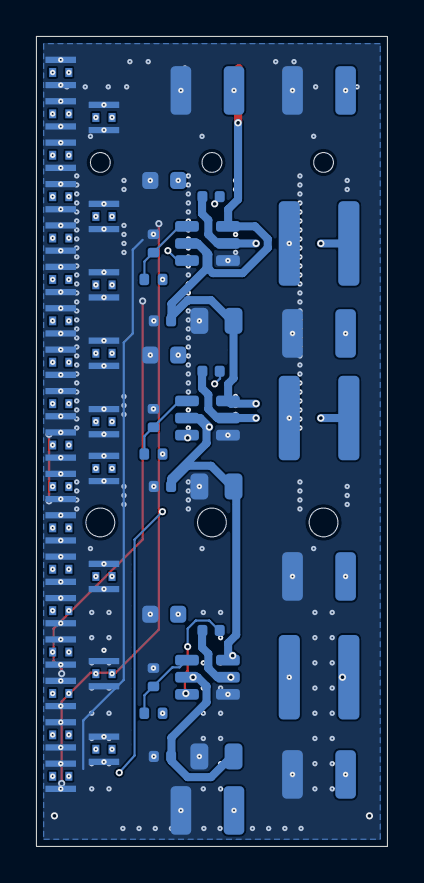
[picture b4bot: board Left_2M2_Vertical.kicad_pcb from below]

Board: 32 copper layers, 19.5 x 45.0 mm, 92 parts (57 on the bottom side), 101 nets.

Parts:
C101, C201, C401: 10uF 25V X7R; C_0805_2012Metric
C102, C202, C402: 100nF 50V; C_0402_1005Metric
C103, C203, C403: 100nF 25V; C_0402_1005Metric
C104, C105, C204, C205, C404, C405: 22uF 16V X7R; C_1210_3225Metric
C106, C206, C406: 1uF 16V; C_0603_1608Metric
C120, C121, C122, C123, C124, C125, C126, C127, C220, C221, C222, C223, C224, C225, C226, C227, C420, C421, C422, C423, C424, C425, C426, C427: 220nF 16V AC; C_0402_1005Metric
J1: M1 SSD / MDT350M01001VT Gen4; Amphenol_MDT350M01001VT_MKey_Vertical_Gen4
J2: M2 SSD / MDT350M01001VT Gen4; Amphenol_MDT350M01001VT_MKey_Vertical_Gen4
J4: M4 SSD / MDT350M01001VT Gen4; Amphenol_MDT350M01001VT_MKey_Vertical_Gen4
J50: 12V protected / GND / 5A design target; Wire_12V_GND_3A
J51: Three x4 port control / 12-wire; Control_12_Wire
J101: M1 TX0; Twinax_85R_Solder_DRAFT
J102: M1 RX0; Twinax_85R_Solder_DRAFT
J103: M1 TX1; Twinax_85R_Solder_DRAFT
J104: M1 RX1; Twinax_85R_Solder_DRAFT
J105: M1 TX2; Twinax_85R_Solder_DRAFT
J106: M1 RX2; Twinax_85R_Solder_DRAFT
J107: M1 TX3; Twinax_85R_Solder_DRAFT
J108: M1 RX3; Twinax_85R_Solder_DRAFT
J109: M1 CLK; Twinax_85R_Solder_DRAFT
J110: M2 TX0; Twinax_85R_Solder_DRAFT
J111: M2 RX0; Twinax_85R_Solder_DRAFT
J112: M2 TX1; Twinax_85R_Solder_DRAFT
J113: M2 RX1; Twinax_85R_Solder_DRAFT
J114: M2 TX2; Twinax_85R_Solder_DRAFT
J115: M2 RX2; Twinax_85R_Solder_DRAFT
J116: M2 TX3; Twinax_85R_Solder_DRAFT
J117: M2 RX3; Twinax_85R_Solder_DRAFT
J118: M2 CLK; Twinax_85R_Solder_DRAFT
J119: M4 TX0; Twinax_85R_Solder_DRAFT
J120: M4 RX0; Twinax_85R_Solder_DRAFT
J121: M4 TX1; Twinax_85R_Solder_DRAFT
J122: M4 RX1; Twinax_85R_Solder_DRAFT
J123: M4 TX2; Twinax_85R_Solder_DRAFT
J124: M4 RX2; Twinax_85R_Solder_DRAFT
J125: M4 TX3; Twinax_85R_Solder_DRAFT
J126: M4 RX3; Twinax_85R_Solder_DRAFT
J127: M4 CLK; Twinax_85R_Solder_DRAFT
L1, L2, L4: 2.2uH XAL5030-222MEC; L_Coilcraft_XAL5030-XXX
R101, R201, R401: 33.2k; R_0402_1005Metric
R102, R110, R111, R202, R210, R211, R402, R410, R411: 10k; R_0402_1005Metric
U21, U22, U24: TPS565201DDCR; SOT-23-6

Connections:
/CABLE12: C101.1, C102.1, C201.1, C202.1, C401.1, C402.1, J50.1, U21.3, U21.5, U22.3, U22.5, U24.3, U24.5
/GND: C101.2, C102.2, C104.2, C105.2, C106.2, C201.2, C202.2, C204.2, C205.2, C206.2, C401.2, C402.2, C404.2, C405.2, C406.2, J1.1, J1.3, J1.9, J1.15, J1.21, J1.27, J1.33, J1.39, J1.45, J1.51, J1.57, J1.69, J1.71, J1.73, J1.75, J1.MP1, J1.MP2, J2.1, J2.3, J2.9, J2.15, J2.21, J2.27, J2.33, J2.39, J2.45, J2.51, J2.57, J2.69, J2.71, J2.73, J2.75, J2.MP1, J2.MP2, J4.1, J4.3, J4.9, J4.15, J4.21, J4.27, J4.33, J4.39, J4.45, J4.51, J4.57, J4.69, J4.71, J4.73, J4.75, J4.MP1, J4.MP2, J50.2, J51.10, J51.11, J51.12, J101.G, J102.G, J103.G, J104.G, J105.G, J106.G, J107.G, J108.G, J109.G, J110.G, J111.G, J112.G, J113.G, J114.G, J115.G, J116.G, J117.G, J118.G, J119.G, J120.G, J121.G, J122.G, J123.G, J124.G, J125.G, J126.G, J127.G, R102.2, R202.2, R402.2, U21.1, U22.1, U24.1
/M1_3V3: C104.1, C105.1, C106.1, J1.2, J1.4, J1.12, J1.14, J1.16, J1.18, J1.70, J1.72, J1.74, L1.2, R101.1, R110.1, R111.1
/M1_BST: C103.1, U21.6
/M1_CLKREQ: J1.52, J51.2, R110.2
/M1_CLK_N: J1.53, J109.N
/M1_CLK_P: J1.55, J109.P
/M1_FB: R101.2, R102.1, U21.4
/M1_PERST: J1.50, J51.1
/M1_RX0_N: J1.41, J102.N
/M1_RX0_P: J1.43, J102.P
/M1_RX1_N: J1.29, J104.N
/M1_RX1_P: J1.31, J104.P
/M1_RX2_N: J1.17, J106.N
/M1_RX2_P: J1.19, J106.P
/M1_RX3_N: J1.5, J108.N
/M1_RX3_P: J1.7, J108.P
/M1_SW: C103.2, L1.1, U21.2
/M1_TX0_N: C121.1, J101.N
/M1_TX0_N_AC: C121.2, J1.47
/M1_TX0_P: C120.1, J101.P
/M1_TX0_P_AC: C120.2, J1.49
/M1_TX1_N: C123.1, J103.N
/M1_TX1_N_AC: C123.2, J1.35
/M1_TX1_P: C122.1, J103.P
/M1_TX1_P_AC: C122.2, J1.37
/M1_TX2_N: C125.1, J105.N
/M1_TX2_N_AC: C125.2, J1.23
/M1_TX2_P: C124.1, J105.P
/M1_TX2_P_AC: C124.2, J1.25
/M1_TX3_N: C127.1, J107.N
/M1_TX3_N_AC: C127.2, J1.11
/M1_TX3_P: C126.1, J107.P
/M1_TX3_P_AC: C126.2, J1.13
/M1_WAKE: J1.54, J51.3, R111.2
/M2_3V3: C204.1, C205.1, C206.1, J2.2, J2.4, J2.12, J2.14, J2.16, J2.18, J2.70, J2.72, J2.74, L2.2, R201.1, R210.1, R211.1
/M2_BST: C203.1, U22.6
/M2_CLKREQ: J2.52, J51.5, R210.2
/M2_CLK_N: J2.53, J118.N
/M2_CLK_P: J2.55, J118.P
/M2_FB: R201.2, R202.1, U22.4
/M2_PERST: J2.50, J51.4
/M2_RX0_N: J2.41, J111.N
/M2_RX0_P: J2.43, J111.P
/M2_RX1_N: J2.29, J113.N
/M2_RX1_P: J2.31, J113.P
/M2_RX2_N: J2.17, J115.N
/M2_RX2_P: J2.19, J115.P
/M2_RX3_N: J2.5, J117.N
/M2_RX3_P: J2.7, J117.P
/M2_SW: C203.2, L2.1, U22.2
/M2_TX0_N: C221.1, J110.N
/M2_TX0_N_AC: C221.2, J2.47
/M2_TX0_P: C220.1, J110.P
/M2_TX0_P_AC: C220.2, J2.49
/M2_TX1_N: C223.1, J112.N
/M2_TX1_N_AC: C223.2, J2.35
/M2_TX1_P: C222.1, J112.P
/M2_TX1_P_AC: C222.2, J2.37
/M2_TX2_N: C225.1, J114.N
/M2_TX2_N_AC: C225.2, J2.23
/M2_TX2_P: C224.1, J114.P
/M2_TX2_P_AC: C224.2, J2.25
/M2_TX3_N: C227.1, J116.N
/M2_TX3_N_AC: C227.2, J2.11
/M2_TX3_P: C226.1, J116.P
/M2_TX3_P_AC: C226.2, J2.13
/M2_WAKE: J2.54, J51.6, R211.2
/M4_3V3: C404.1, C405.1, C406.1, J4.2, J4.4, J4.12, J4.14, J4.16, J4.18, J4.70, J4.72, J4.74, L4.2, R401.1, R410.1, R411.1
/M4_BST: C403.1, U24.6
/M4_CLKREQ: J4.52, J51.8, R410.2
/M4_CLK_N: J4.53, J127.N
/M4_CLK_P: J4.55, J127.P
/M4_FB: R401.2, R402.1, U24.4
/M4_PERST: J4.50, J51.7
/M4_RX0_N: J4.41, J120.N
/M4_RX0_P: J4.43, J120.P
/M4_RX1_N: J4.29, J122.N
/M4_RX1_P: J4.31, J122.P
/M4_RX2_N: J4.17, J124.N
/M4_RX2_P: J4.19, J124.P
/M4_RX3_N: J4.5, J126.N
/M4_RX3_P: J4.7, J126.P
/M4_SW: C403.2, L4.1, U24.2
/M4_TX0_N: C421.1, J119.N
/M4_TX0_N_AC: C421.2, J4.47
/M4_TX0_P: C420.1, J119.P
/M4_TX0_P_AC: C420.2, J4.49
/M4_TX1_N: C423.1, J121.N
/M4_TX1_N_AC: C423.2, J4.35
/M4_TX1_P: C422.1, J121.P
/M4_TX1_P_AC: C422.2, J4.37
/M4_TX2_N: C425.1, J123.N
/M4_TX2_N_AC: C425.2, J4.23
/M4_TX2_P: C424.1, J123.P
/M4_TX2_P_AC: C424.2, J4.25
/M4_TX3_N: C427.1, J125.N
/M4_TX3_N_AC: C427.2, J4.11
/M4_TX3_P: C426.1, J125.P
/M4_TX3_P_AC: C426.2, J4.13
/M4_WAKE: J4.54, J51.9, R411.2

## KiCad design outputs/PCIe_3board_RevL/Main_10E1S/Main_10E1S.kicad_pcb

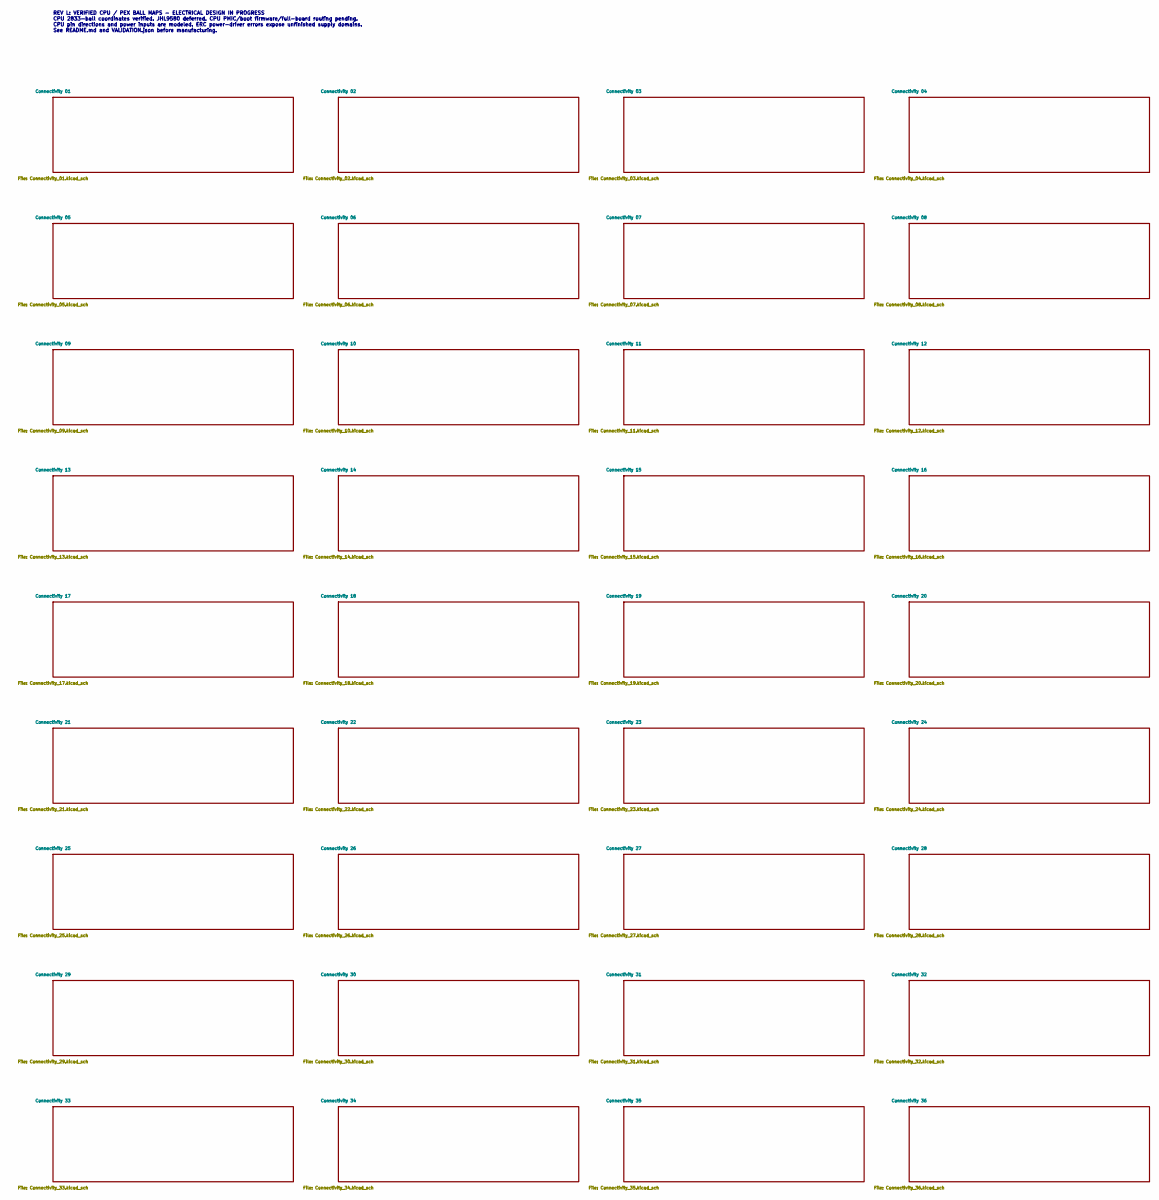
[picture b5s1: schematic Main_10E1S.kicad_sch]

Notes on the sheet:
REV L: VERIFIED CPU / PEX BALL MAPS - ELECTRICAL DESIGN IN PROGRESS CPU 2833-ball coordinates verified. JHL9580 deferred. CPU PMIC/boot firmware/full-board routing pending. CPU pin directions and power inputs are modeled. ERC power-driver errors expose unfinished supply domains. See README.md and V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
